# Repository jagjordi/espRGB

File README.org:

* espRGB
An ESP8266-based RGB LED controller using [[https://esphome.io][ESPhome.io]]

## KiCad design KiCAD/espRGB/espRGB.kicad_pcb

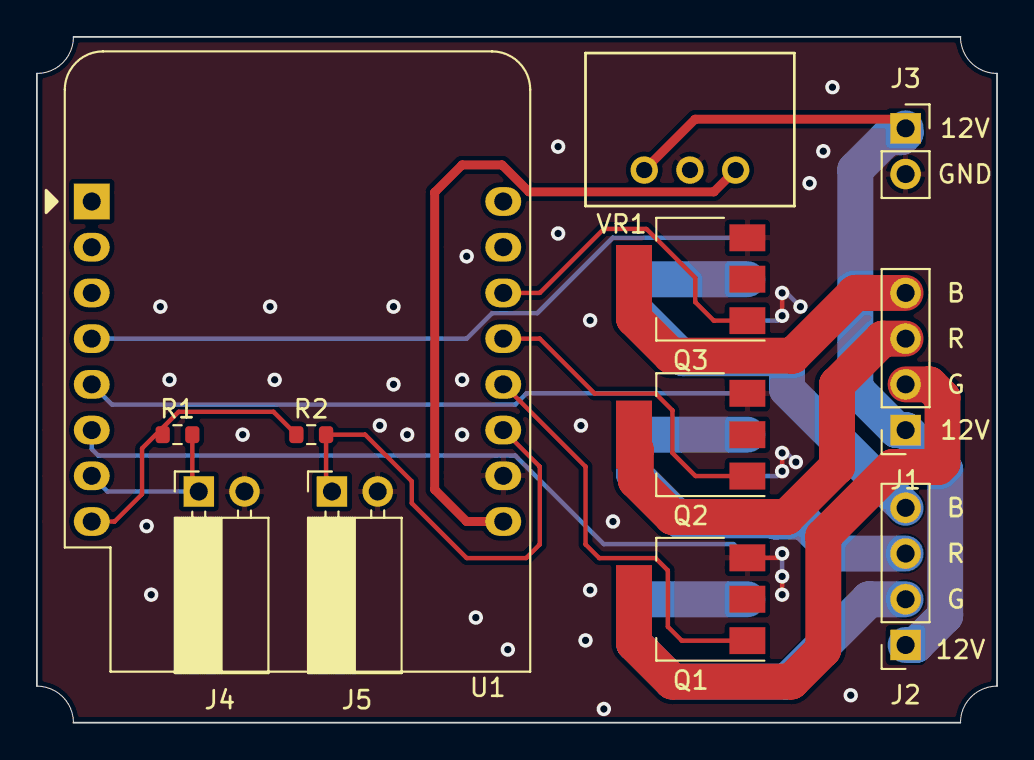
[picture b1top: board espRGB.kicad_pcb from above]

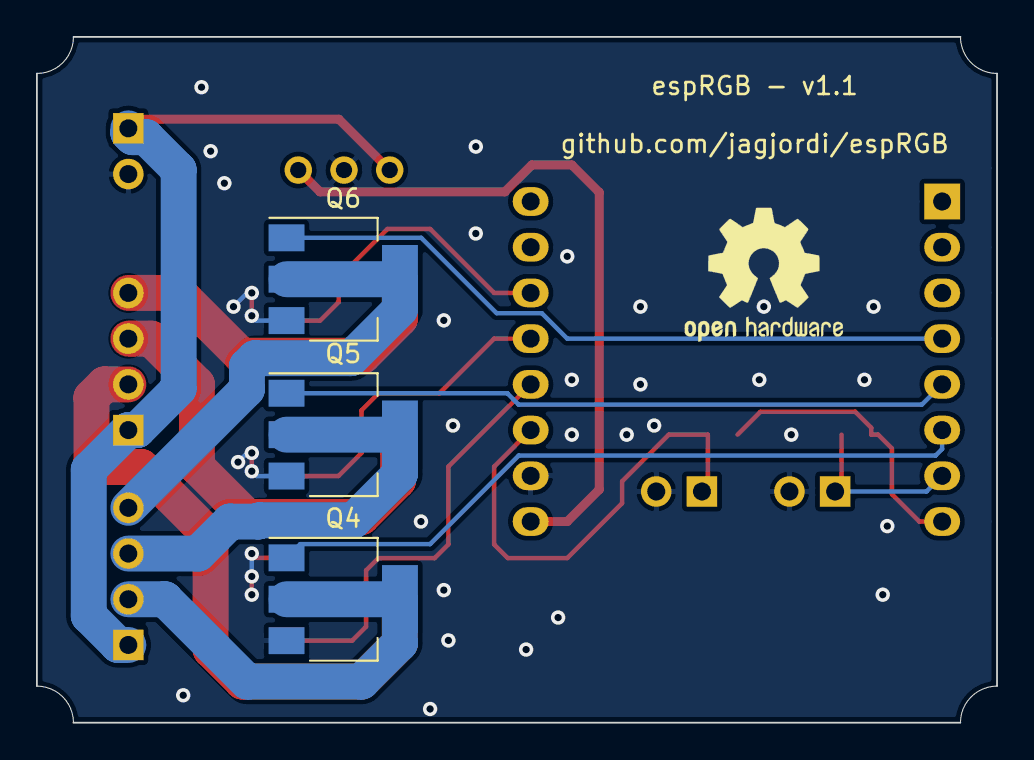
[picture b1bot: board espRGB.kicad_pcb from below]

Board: 2 copper layers, 53.3 x 38.1 mm, 15 parts (3 on the bottom side), 18 nets.

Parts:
J1, J2: Conn_01x04_Female; PinSocket_1x04_P2.54mm_Vertical
J3: Conn_01x02_Female; PinSocket_1x02_P2.54mm_Vertical
J4, J5: Conn_01x02_Female; PinSocket_1x02_P2.54mm_Horizontal
Q1, Q2, Q3, Q4, Q5, Q6: Q_NMOS_GDS; SOT-223-3_TabPin2
R1, R2: R; R_0603_1608Metric
U1: WeMos_D1_mini; WEMOS_D1_mini_light
VR1: Wurth-FDSM

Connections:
+3V3: R1.1, R2.1, U1.8
+5V: U1.9, VR1.3
+12V: J1.1, J2.1, J3.1, VR1.1
/blue1: J2.4, Q6.2
/blue1_gate: Q6.1, U1.4
/blue2: J1.4, Q3.2
/blue2_gate: Q3.1, U1.14
/button1: J4.1, R1.2, U1.7
/button2: J5.1, R2.2, U1.11
/green1: J2.2, Q4.2
/green1_gate: Q4.1, U1.6
/green2: J1.2, Q1.2
/green2_gate: Q1.1, U1.12
/red1: J2.3, Q5.2
/red1_gate: Q5.1, U1.5
/red2: J1.3, Q2.2
/red2_gate: Q2.1, U1.13
GND: J3.2, J4.2, J5.2, Q1.3, Q2.3, Q3.3, Q4.3, Q5.3, Q6.3, U1.10, VR1.2

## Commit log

2020-07-28 added BOM
2020-12-16 done?
2020-12-29 v1.1
